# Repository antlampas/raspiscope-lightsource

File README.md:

# Raspiscope Light Source Circuit

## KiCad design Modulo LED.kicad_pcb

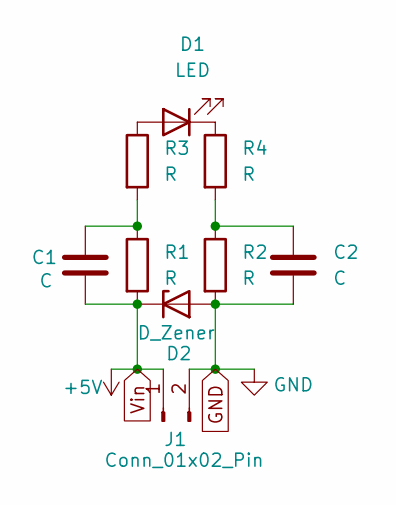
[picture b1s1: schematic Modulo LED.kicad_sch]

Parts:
C1, C2: C; C_0603_1608Metric
D1: LED; LED_0201_0603Metric
D2: D_Zener; D_0603_1608Metric
J1: Conn_01x02_Pin; PinHeader_1x02_P1.00mm_Vertical
R1, R2, R3, R4: R; R_0201_0603Metric

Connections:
GND: C2.2, D2.2 (A), J1.2, R2.2
unnamed: C1.1, R1.1, R3.2
unnamed: C2.1, R2.1, R4.2
unnamed: D1.2 (A), R3.1
unnamed: D1.1 (K), R4.1
Vin: C1.2, D2.1 (K), J1.1, R1.2

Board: 2 copper layers, 9 parts (0 on the bottom side), 6 nets, no tracks yet.

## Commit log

2025-07-19 Added License and README
2025-07-20 Removed my local chace file
2025-07-29 Added filters and overvoltage protecion circuit
